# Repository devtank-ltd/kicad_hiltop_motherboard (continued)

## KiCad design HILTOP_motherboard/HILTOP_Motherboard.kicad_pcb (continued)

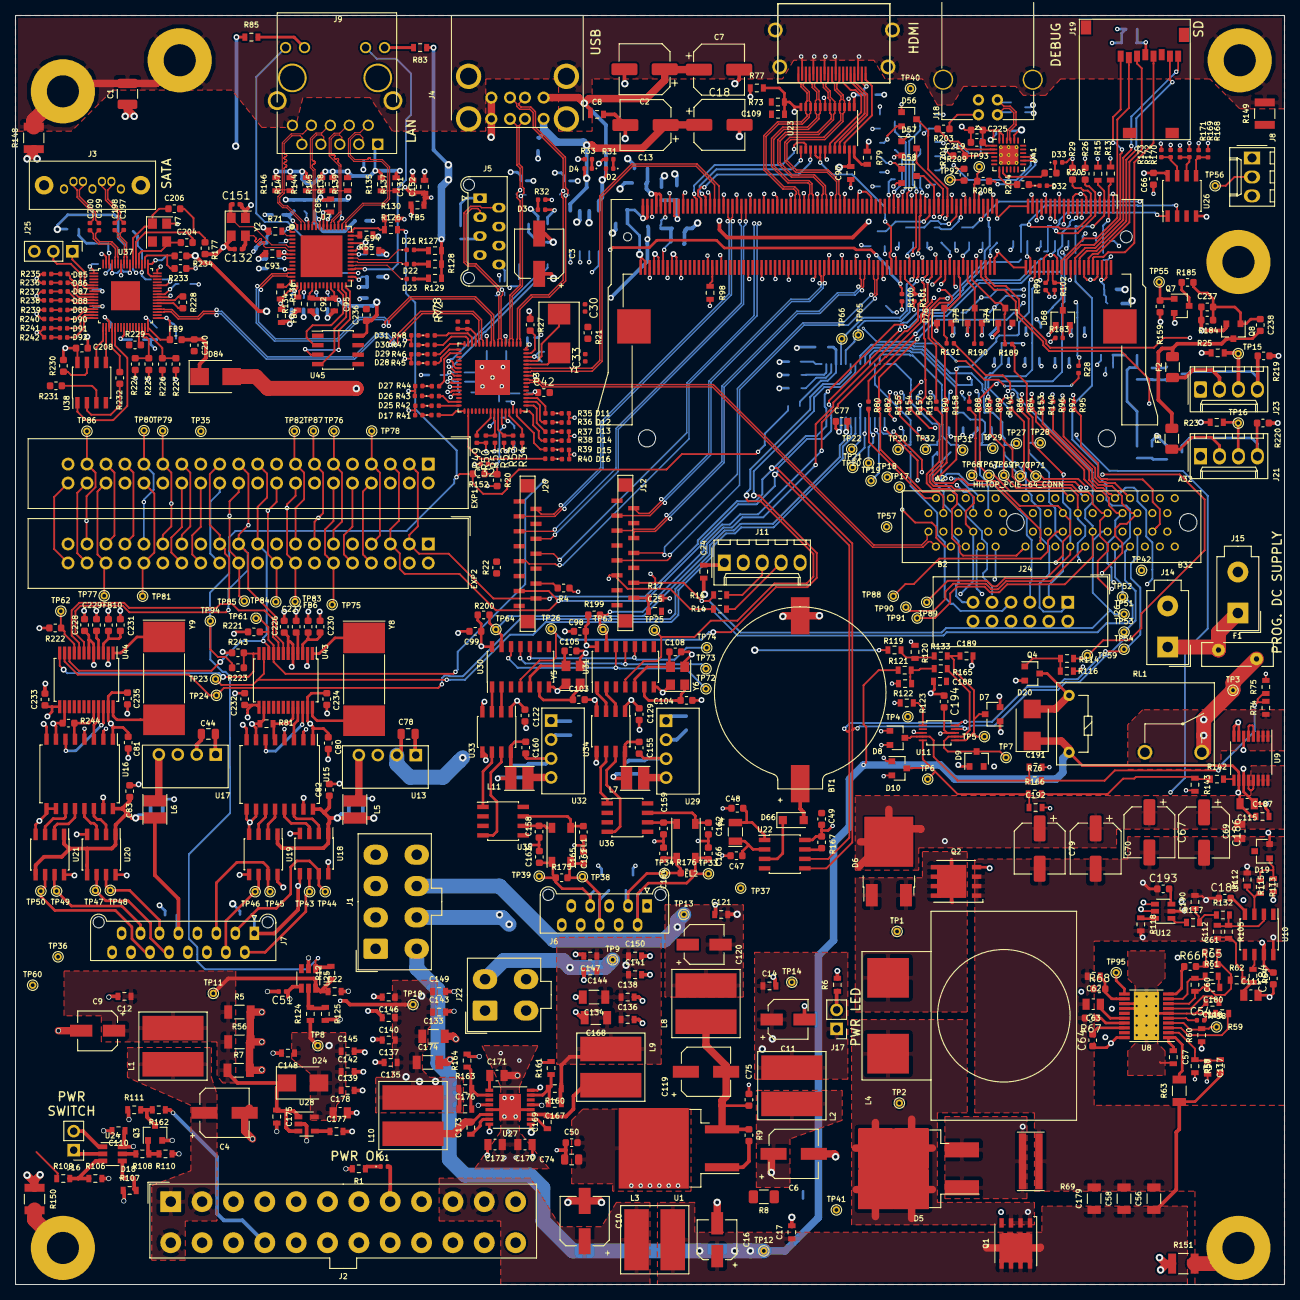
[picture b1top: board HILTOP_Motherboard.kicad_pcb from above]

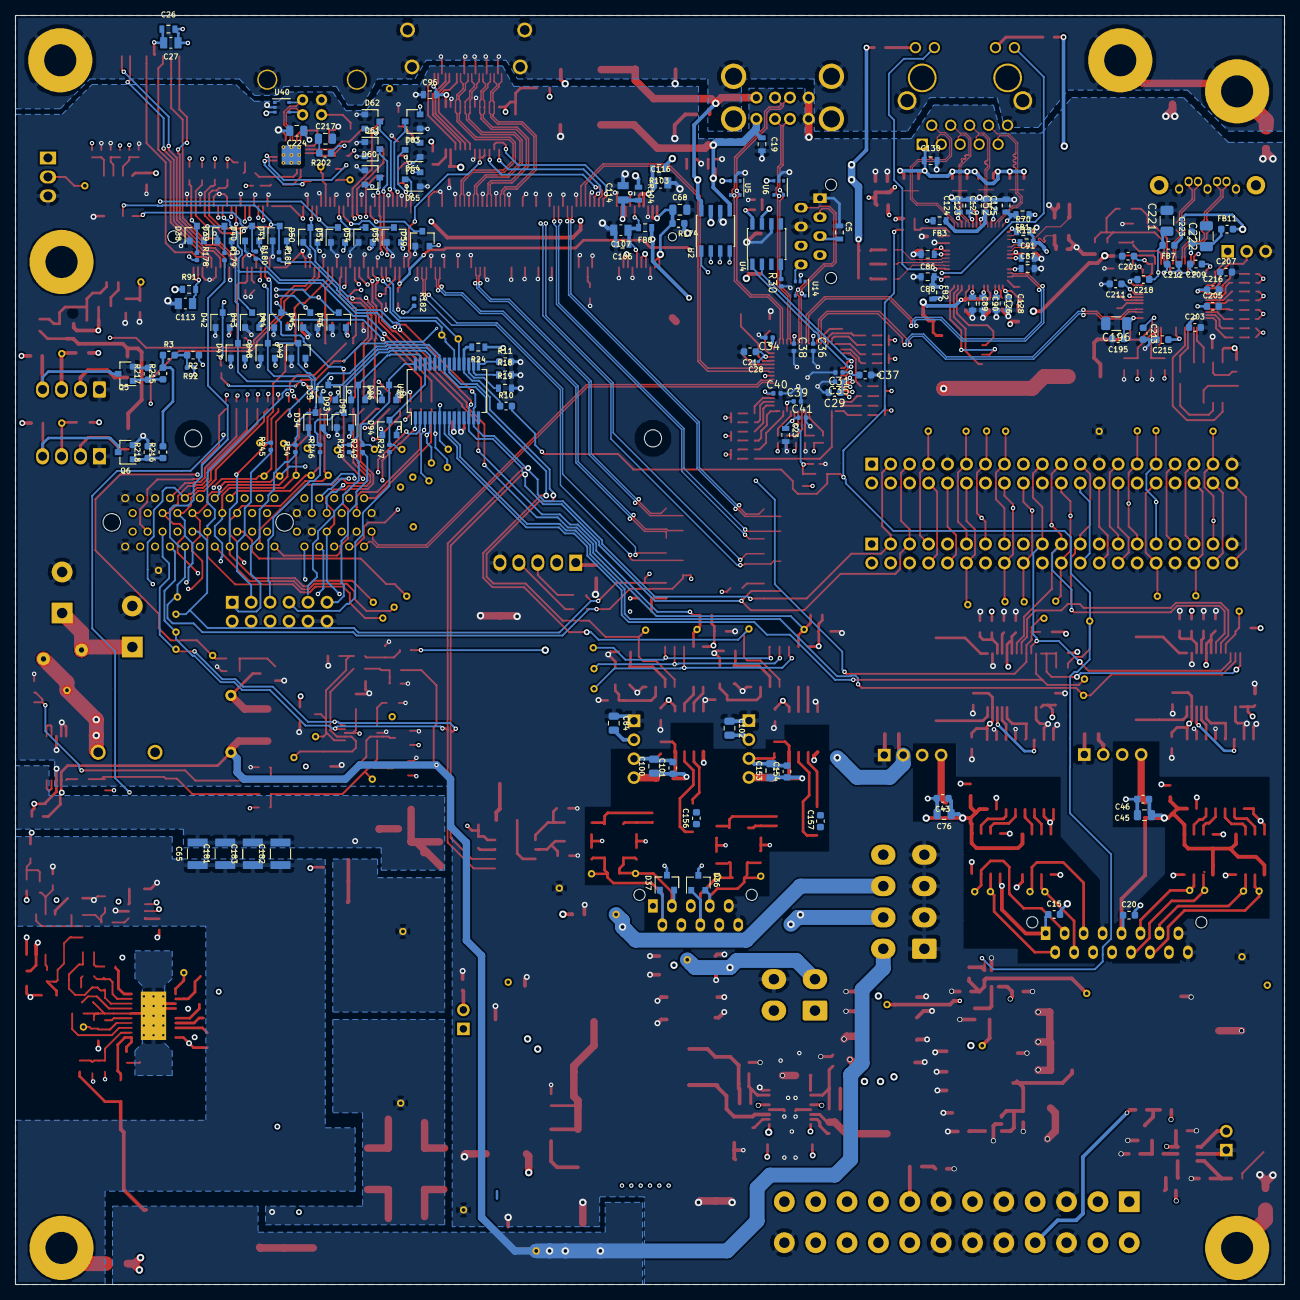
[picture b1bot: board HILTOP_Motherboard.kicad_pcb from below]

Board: 6 copper layers, 170.0 x 170.0 mm, 752 parts (151 on the bottom side), 473 nets.

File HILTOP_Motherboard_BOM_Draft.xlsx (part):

Title | HILTOP Motherboard
Revision | Issue 1
Date | 2019-01-10
Generated | Mon 14 Jan 2019 09:19:05 GMT
Company | Devtank Ltd
Comment 1
Comment 2
Comment 3
Comment 4
Total Parts | 752
Total Unique Parts | 166
Ref | Qty | Value | Footprint | Devtank | Description | Manufacturer | Manufacturer Part Number | Supplier | Supplier Part number | Cost (unit) | Cost (total)
BT1 | 1 | Battery_Cell | Devtank_PCB_Lib:BatteryHolder_Keystone_1061_1x20mm | 750-001 | Keystone 1061_1x20mm Battery Holder, PCB Mount | Keystone | 1061 | Farnell | 1282702 | 1.19 | 1.19
C8 C22 C26 C25 C24 C12 C14 C17 C121 C5 C19 C15 C20 C50 C75 C77 C23 C123 C124 C1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 | 113 | 100nF | Capacitor_SMD:C_0603_1608Metric | 105-002 | 100nF 50V X7R | Kemet | C0603C104M5RACTU | Farnell | 2581046 | 0.0297 | 3.3561
C27 C107 C114 C116 C113 C68 C100 C153 C217 C224 C76 C45 | 12 | 4.7uF | Capacitor_SMD:C_0805_2012Metric | 105-007 | 4.7uF 16V X7R | muRata | GCJ21BR71C475KA01L | Farnell | 2781412 | 0.475 | 5.7
C4 C10 C119 C6 | 4 | 10uF | Capacitor_SMD:CP_Elec_6.3x5.3 | 108-002 | 10uF 50V KZ, V-Chip Series | Multicomp | MCVKZ050M100EA1L | Farnell | 2611344 | 0.146 | 0.584
C9 C11 C16 C120 | 4 | 4.7uF | Capacitor_SMD:CP_Elec_5x5.3 | 108-001 | 4.7uF 50V KZ, V-Chip Series | Multicomp | MCVKZ050M4R7DA1L | Farnell | 2611348 | 0.12 | 0.48
C51 C32 C35 C28 C39 C34 C31 C36 C38 C40 C41 C52 | 12 | 100nF | Capacitor_SMD:C_0402_1005Metric | 105-019 | 100nF 50V X7R | TDK | C1005X7R1H104M050BB | Farnell | 2525048 | 0.0744 | 0.8928
C3 C18 C7 C13 C2 C67 C186 C70 C79 | 9 | 100uF | Capacitor_SMD:CP_Elec_6.3x7.7 | 108-003 | 100uF 50V 0.34R FT Series | Panasonic | EEEFTH101XAP | Farnell | 1868426 | 0.459 | 4.131
C1 | 1 | 100nF | Capacitor_SMD:C_1210_3225Metric | 105-020 | 100nF 50V X7R | AVX | 12101C104KAT2A | Farnell | 1327731 | 0.28 | 0.28
C74 C171 C63 C115 C111 | 5 | 1uF | Capacitor_SMD:C_0805_2012Metric | 105-004 | 1uF 16V X7R | Walsin | 0805B105K160CT | Farnell | 2496946 | 0.052 | 0.26
C30 C33 C151 C132 | 4 | 18pF | Capacitor_SMD:C_0402_1005Metric | 106-010 | 18pF COG/NPO | AVX | 04025A180JAT2A | Farnell | 1740572 | 0.133 | 0.532
C21 C29 C37 C42 C175 C195 C227 C229 | 8 | 1uF | Capacitor_SMD:C_0603_1608Metric | 105-014 | 1uF 16V X7R | Walsin | 0603B105K160CT | Farnell | 2496835 | 0.298 | 2.384
C131 C177 | 2 | 10nF | Capacitor_SMD:C_0603_1608Metric | 105-006 | 10nF 50V X7R | Kemet | C0603C103K5RACTU | Farnell | 1414609 | 0.0117 | 0.0234
C130 C167 C176 C61 C62 C112 C237 C238 | 8 | DNF | Capacitor_SMD:C_0603_1608Metric |  |  |  |  |  |  |  | 0
C48 C47 | 2 | 12pF | Capacitor_SMD:C_0603_1608Metric | 106-009 | 12pF 50V COG/NPO | AVX | 06035A120JAT2A | Farnell | 1462447 | 0.0744 | 0.1488
C133 C134 C174 C168 C221 C222 C196 | 7 | 22uF | Capacitor_SMD:C_1206_3216Metric | 105-003 | 22uF 10V X7R | Kemet | C1206C226M8RACTU | Farnell | 2118135 | 0.351 | 2.457
C178 C84 C102 C78 C44 | 5 | 2.2uF | Capacitor_SMD:C_0805_2012Metric | 105-005 | 2.2uF 16V X7R | Kemet | C0805C225K4RACAUTO | Farnell | 2070473 | 0.276 | 1.38
C170 C172 | 2 | 10uF | Capacitor_SMD:C_0805_2012Metric | 105-001 | 10uF 16V X5R 10% MLCC | AVX | 0805YD106KAT2A | Farnell | 1658880 | 0.148 | 0.296
C56 C58 C179 | 3 | 2.2uF | Capacitor_SMD:C_1206_3216Metric | 105-011 | 2.2uF 25V X7R | Yageo | CC1206KKX7R8BB225 | Farnell | 1458911 | 0.286 | 0.858
C54 | 1 | 330pF | Capacitor_SMD:C_0201_0603Metric | 106-001 | 330pF 100V COG/NPO | Kemet | C0603C331J5GACTU | Farnell | 1414634 | 0.615 | 0.615
C65 C181 C182 C183 | 4 | 4.7uF | Capacitor_SMD:C_1210_3225Metric | 105-008 | 4.7uF 50V X7R | AVX | 12105C475KAT2A | Farnell | 1658891 | 0.662 | 2.648
C69 | 1 | 470nF | Capacitor_SMD:C_0805_2012Metric | 105-009 | 470nF 100V X7R | AVX | 08051C474K4Z2A | Farnell | 1867963 | 0.384 | 0.384
C162 C159 C164 C166 C161 C158 C163 C165 | 8 | 47pF | Capacitor_SMD:C_0603_1608Metric | 106-011 | 47pF COG/NPO | AVX | 06035A470JAT2A | Farnell | 498567 | 0.063 | 0.504
C103 C105 C104 C108 C206 C204 | 6 | 9pF | Capacitor_SMD:C_0603_1608Metric | 106-008 | 9pF 50V COG/NPO | TDK | C1608C0G1H090C080AA | Farnell | 2526242 | 0.08 | 0.48
C101 C154 C43 C46 | 4 | 470pF | Capacitor_SMD:C_0603_1608Metric | 106-007 | 470pF 50V COG/NPO | AVX | 06035A471JAT2A | Farnell | 316672 | 0.108 | 0.432
C197 C198 C199 C200 | 4 | 10nF | Capacitor_SMD:C_0402_1005Metric | 105-017 | 10nF 50V X7R | AVX | 04025C103KAT2A | Farnell | 2332514 | 0.0411 | 0.1644
D1 D11 D13 D15 D17 D26 D28 D30 D23 D22 D21 D18 D85 D86 D87 D88 D89 D90 D91 D92 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 | 22 | GRN | LED_SMD:LED_0402_1005Metric | 110-005 | LED GREEN CLEAR 1006 SMD | Rohm Semiconductor | SML-P13PTT86R | Digikey | 846-1197-1-ND | 0.31 | 6.82
D34 D35 D93 D94 D95 D96 D38 D39 D40 D41 D42 D43 D44 D45 D47 D48 D49 D46 D50 D51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 | 40 | BAV99 | Package_TO_SOT_SMD:SOT-23 | 134-001 | BAV99 - Small Signal Diode, Dual Series, 75 V, 300 mA, 1.25 V, 4 ns, 4.5 | Diodes Inc | BAV99 | Farnell | 1902422 | 0.086 | 3.44
D12 D14 D16 D25 D27 D29 D31 | 7 | YEL | LED_SMD:LED_0402_1005Metric | 110-007 | LED GREEN-YELLOW CLEAR 1006 SMD | Rohm Semiconductor | SML-P11MTT86R | Digikey | 846-1211-1-ND | 0.43 | 3.01
D2 D4 D3 | 3 | RED | LED_SMD:LED_0402_1005Metric | 110-004 | LED RED CLEAR 0402 SMD | Rohm Semiconductor | SML-P12VTT86R | Digikey | 846-1168-6-ND | 0.4 | 1.2
D66 | 1 | MBR230LSFT | Diode_SMD:D_SOD-123F | 133-006 | Schottky Rectifier, 30 V, 2 A, Single, SOD-123FL | ON Semi | MBR230LSFT1G | Farnell | 2317422 | 0.26 | 0.26
D24 D20 | 2 | STPS1L30 | Diodes_SMD:D_SMB | 133-001 | STPS1L30 Low Drop Power Schottky Diode (300mV max) | ST Microelectronics | STPS1L30 | Farnell | 1467550 | 0.158 | 0.316
D6 | 1 | MBRD1035 | Devtank_PCB_Lib:DPAK | 133-003 | MBRD1035CTL Schottky Power Rectifier | On Semi | MBRD1035CTL | Farnell | 9556974 | 0.757 | 0.757
D5 | 1 | VB40100C | Devtank_PCB_Lib:TO-263AB | 133-002 | Dual High Voltage Trench MOS barrier Schottky Rectifier | Vishay | VB40100C-E3/4W | Farnell | 2335186 | 2.4 | 2.4
D19 | 1 | LM4040 | Package_TO_SOT_SMD:SOT-23 | 138-001 | LM4040CYM3-2.5V Reference | Microchip | LM4040CYM3-2.5 | Farnell | 2509863 | 0.21 | 0.21
D37 D36 | 2 | NUP2105L | Package_TO_SOT_SMD:SOT-23 | 136-002 | TVS DIODE – CAN BUS | ON Semi | NUP2105LT1G | Digikey | NUP2105LT1GOSCT-ND | 0.36 | 0.72
D84 | 1 | STPS1L30 | Diode_SMD:D_SMB | 133-001 | STPS1L30 Low Drop Power Schottky Diode (300mV max) | ST Microelectronics | STPS1L30 | Farnell | 1467550 | 0.158 | 0.158
EXP1 EXP2 | 2 | CONN_02X20 | Connector_IDC:IDC-Header_2x20_P2.54mm_Vertical | 710-007 | 40 Way 2.54mm Box Header | Amphenol | T821140A1S100CEU | Farnell | 2215314 | 0.521 | 1.042
F1 | 1 | PPTC 3.8A | Fuse:Fuse_Bourns_MF-RHT200 | 190-001 | PPTC Resettable Fuse, Through Hole, MF-RHT Series, 2 A, 3.8 A, 32 V, -40 °C | Bourns Inc | MF-RHT200/32-2 | Farnell | 2810350 | 0.611 | 0.611
F3 F2 | 2 | Polyfuse | Fuse:Fuse_1206_3216Metric | 190-002 | PPTC Resettable Fuse, SMD, POLYFUSE 1206L | Littlefuse | 1206L050/15YR | Farnell | 2752736 | 0.367 | 0.734
FB1 FB2 FB3 FB4 FB5 FB8 FB7 FB9 FB11 FB6 FB10 | 11 | 120R_100MHz | Resistor_SMD:R_0603_1608Metric | 113-001 | 120Ohm, 100MHz Ferrite Bead | muRata | BLM18AG121SN1D | Farnell | 1515672 | 0.0415 | 0.4565
FL2 FL1 | 2 | PE-1812ACC510STS | Devtank_PCB_Lib:Inductor_PE-1812ACCXXXSTS | 114-001 | CMC 230MA 2LN 3.5 KOHM AEC-Q200 | Pulse Electronics | PE-1812ACC510STS | Digikey | 553-2565-1-ND | 0.73 | 1.46
J10 | 1 | HDMI | Devtank_PCB_Lib:FCI_10029449-11RLF | 702-001 | HDMI Connector – PCB Mount | Amphenol | 47151-1051 | Digikey | 609-4614-1-ND | 0.57 | 0.57
J11 | 1 | DISP_PWR | Connector_Molex:Molex_KK-254_AE-6410-05A_1x05_P2.54mm_Vertical | 710-016 | 5 Way Header KK Series | Molex | 22-27-2051 | Farnell | 9731679 | 0.251 | 0.251
J19 | 1 | Micro_SD_Card | Devtank_PCB_Lib:uSD_MSDC-PP03 | 705-002 | uSD Valcon Push-push type MSDC-PP-03 | Valcon | MSDC-PP-03 | Toby | MSDC-PP-03 | 0.99 | 0.99
J12 | 1 | DISPLAY_PORT | Devtank_PCB_Lib:DSI_FCC15W_VERT | 702-003 | Vertical 15Way FFC Connector, 1mm | Valcon | FFC1-15-V-TR | Toby | FFC115VTR | 0.33 | 0.33
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
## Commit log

2018-01-26 Setup common libraries for my Kicad project.
2018-01-26 Project setup - ready for development
2018-02-25 Added new USB2.0 device
2018-02-26 add SP3003 ESD protection diodes to USB circuit
2018-02-26 Added RTC and Temp Sensor
2018-02-27 Added TUSB9260 SATA bridge device
2018-02-27 Added more detail for SATA bridge chip circuit
2018-03-09 Fixed giabit LAN Schematic errors
2018-03-09 Added more detail to motherboard schemas
2018-05-03 Finished CAN nd RS485 interface circuits
2018-05-03 Updated pinouts for Backplane and Compute Module
2018-05-08 Furthe progress on Schematics, assigned all main footprints using latest libraries, removed unwanted tracking and parts from original PCB layout
2018-12-21 Schematics complete - 1st draft
2018-12-21 Schematics complete - 1st draft2
2019-01-04 BOM nearly complete!
2019-01-09 nearly finished placing all parts!
2019-01-11 All parts placed and backplane connector checked and locked
2019-01-14 DRC checks complete, all errors and warnings cleared. BOM created and parts rationalised.
2019-01-14 tracking updates
2019-01-25 90% complete on backplane and IO connectors
2019-02-01 nearly all tracked - power and ground planes to do!
2019-02-04 nearly there, drc errors all resolved!
2019-06-28 Rev A complete!
2019-07-02 Put project under Cern ohl version 1.2 license.
2019-07-02 Change common submodule to be relatively pathed.
2019-07-02 Fix gitignore
2019-07-02 To tracking backup files now gitignore is fixed.
2019-07-03 finished new tracking for RS485 signals and general house keeping
2019-07-10 Replaced FCC 15way connectors with new footprint
2020-02-09 Rev B
2020-04-28 Rev C - pre-release
2021-02-10 Moved Backplane Connctor 2mm to the left to fix alignment issue on HILTOP 63HP
2021-02-10 added small fixes for USB Debug chip to allow independant power up from external cable
2021-02-12 updates to include - license, remove U46, swap crystal Y1
2021-02-17 Added TVS diodes on PSU inputs, update license details
2021-02-17 problem with gerber export!
2021-02-17 changed silkscreen to revD and updated sheet information
2021-03-05 fixed component pos data for CM and minor updates to BOM to remove depreciated parts
2021-03-15 Tidy up documentation ready for public release
2021-03-15 Use merged common lib
2021-03-16 Updated some 3D footprint filepaths
